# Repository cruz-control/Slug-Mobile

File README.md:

# Slug-Mobile

Slug Mobile: One Tenth Scale Autonomous Vehicle

CARLA gym environment: <https://github.com/cruz-control/carla-gym-env.git>

## Get Stated

Run the following command to install all the dependencies

```bash
pip3 install -r requirements.txt
```

Next you can run `main.py` to start the code.

## Setup Car

### Sensor Mount

Here's a link to the CAD for the sensor mount: [OnShape Link](https://cad.onshape.com/documents/b2439afa538affcdb2ce625c/w/6e13cd6ddc2a3739fa3b2738/e/3fdea52f99cf651c55640d90?renderMode=0&uiState=669d97643e0ca32c1d4d6b9b)

### Electrical System

We have included the custom power distribution board we created to the `power_dist_board` folder, the schematics show how to connect the different components.

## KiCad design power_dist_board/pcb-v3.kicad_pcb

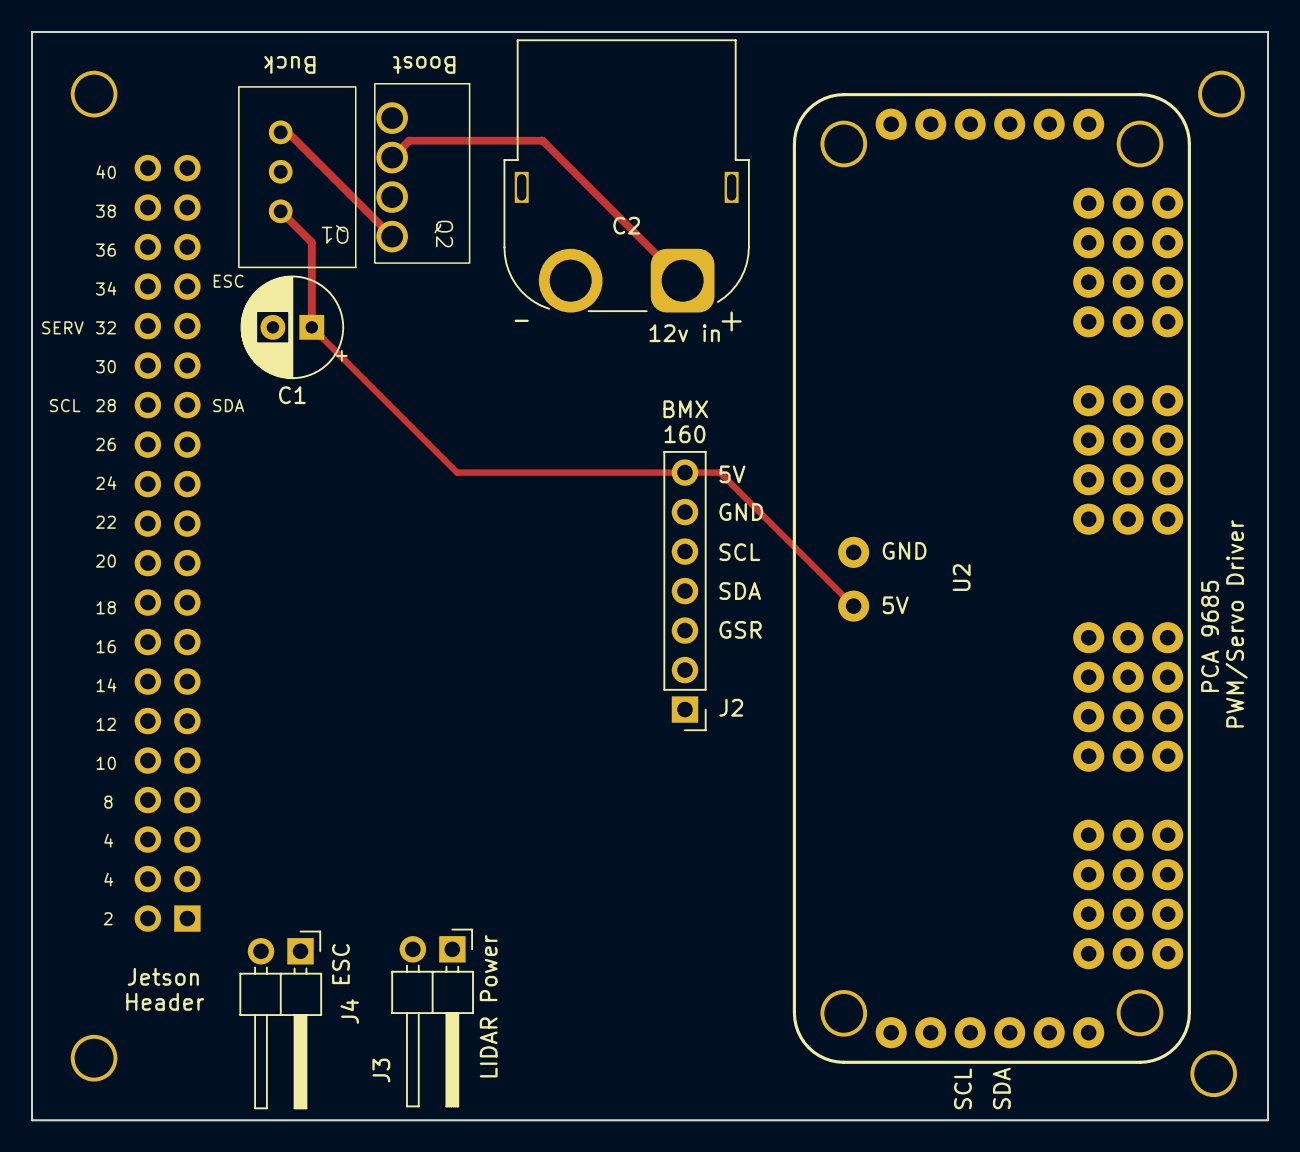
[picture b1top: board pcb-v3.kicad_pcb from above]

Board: 4 copper layers, 79.5 x 70.0 mm, 9 parts (1 on the bottom side), 8 nets.

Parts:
C1: CP_Radial_D6.3mm_P2.50mm
C2: AMASS_XT60PW-F_1x02_P7.20mm_Horizontal
J2: Conn_01x07_Socket; PinHeader_1x07_P2.54mm_Vertical
J3, J4: Screw_Terminal_01x02; PinHeader_1x02_P2.54mm_Horizontal
J5: Conn_02x20_Odd_Even; PinSocket_2x20_P2.54mm_Vertical
Q1: LC78_05-3.0
Q2: CRE1S Boost Converter
U2: Adafruit PCA9685 rev C (1)

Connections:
+3.3V: J5.1, J5.17
+5V: C1.1, J2.7, Q1.3 (Vout), U2.24 (A5)
+12V: C2.1 (Vin), Q2.2 (+Vin)
ESC: J4.1, J5.33
GND: C1.2, C2.2 (Vout), J2.3, J2.6, J3.2, J4.2, J5.6, J5.9, J5.14, J5.20, J5.25, J5.30, J5.34, J5.39, Q1.2 (GND), Q2.1 (-Vin), Q2.3 (-Vout), U2.14 (GND), U2.25 (EXTCLK)
SCL: J2.5, J5.28, U2.4 (A3)
SDA: J2.4, J5.27, U2.3 (A2)
STABLE_12V: J3.1, Q1.1 (Vin), Q2.4 (+Vout)

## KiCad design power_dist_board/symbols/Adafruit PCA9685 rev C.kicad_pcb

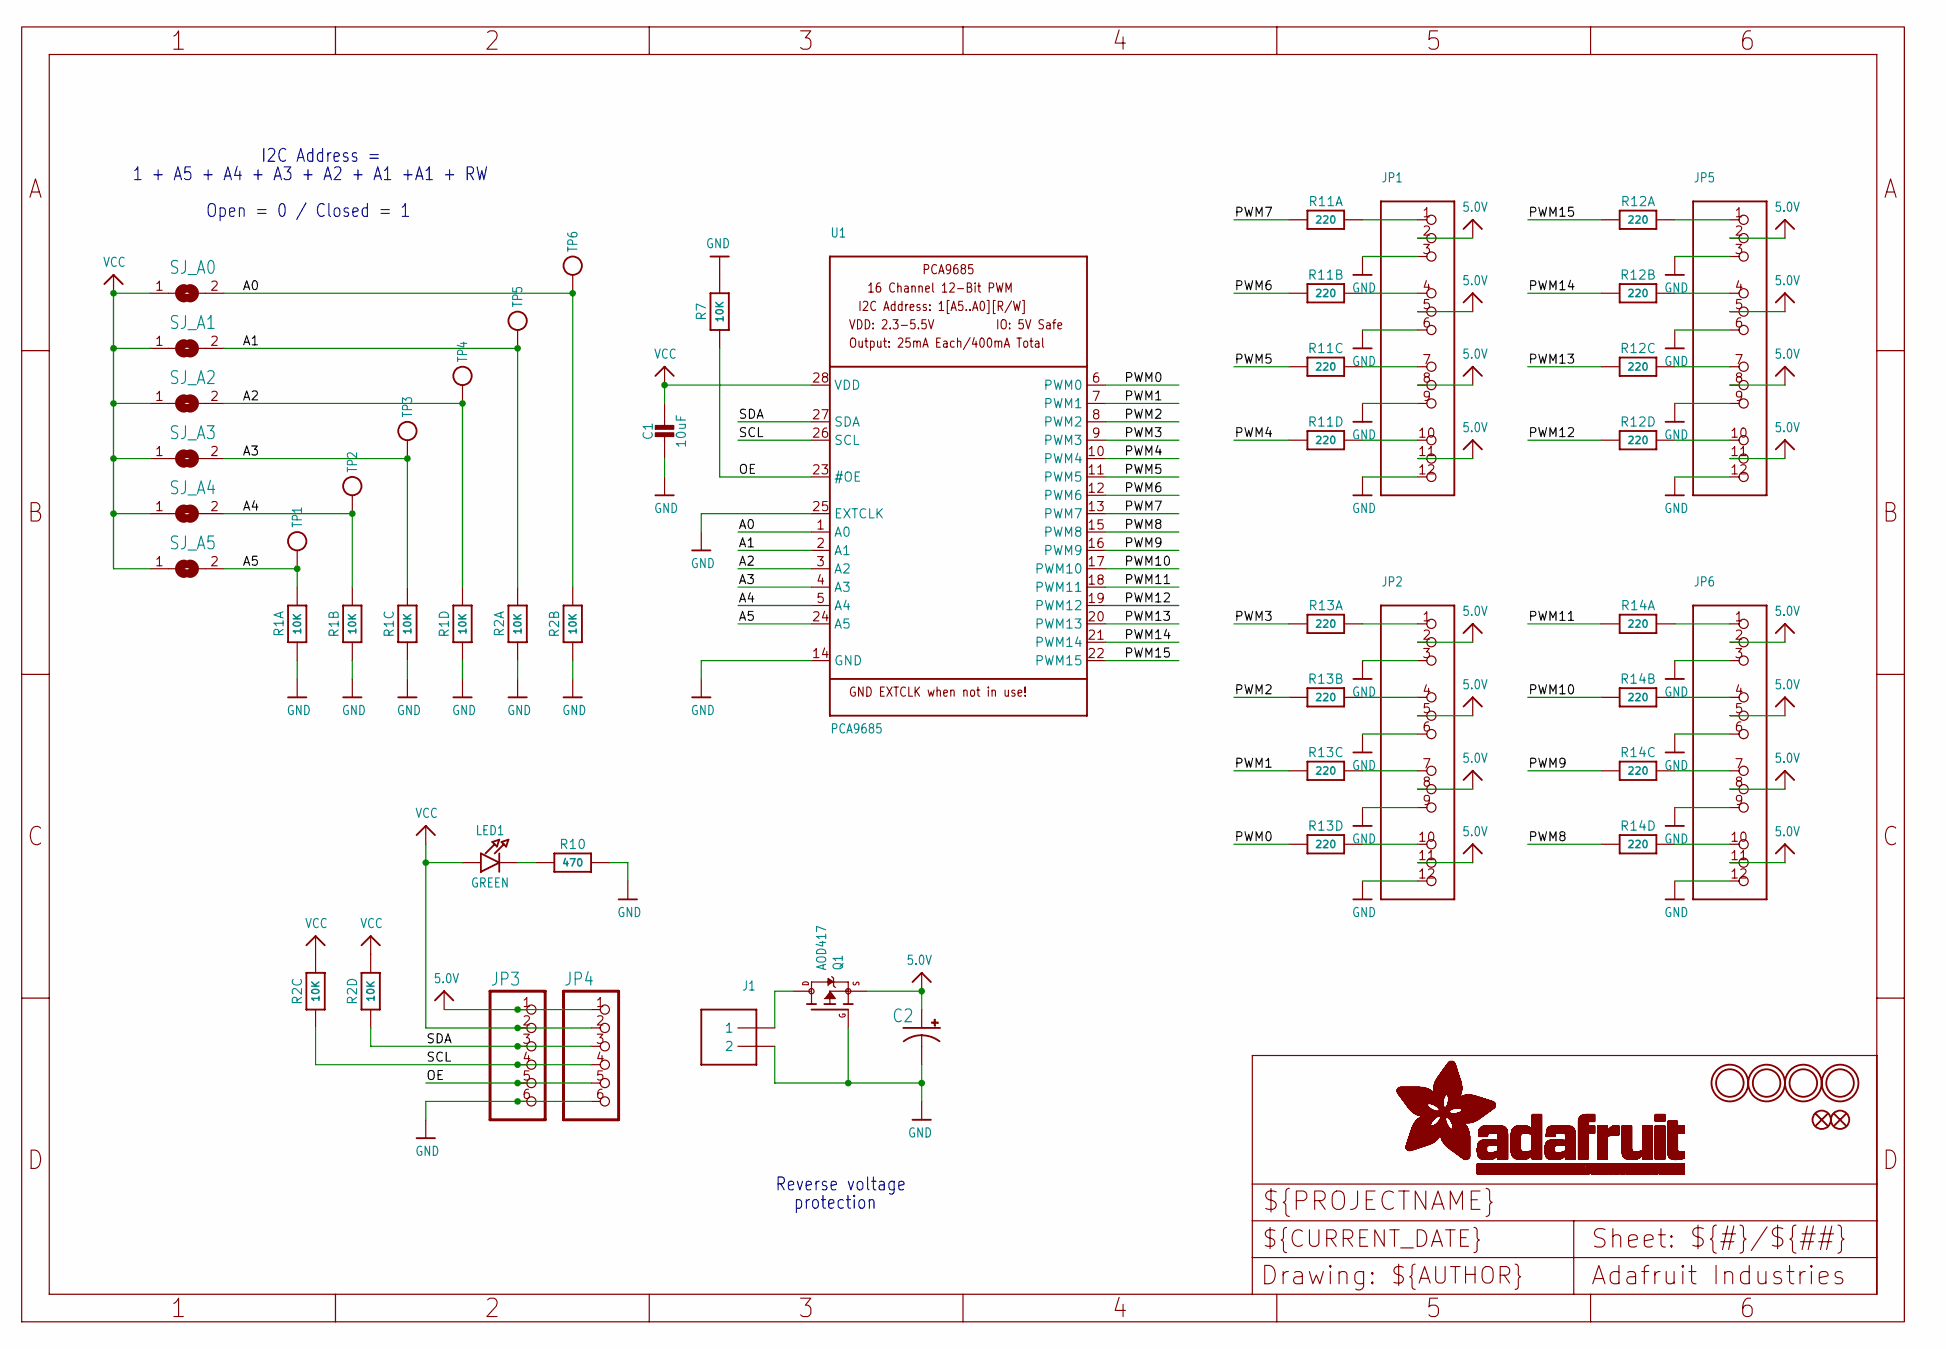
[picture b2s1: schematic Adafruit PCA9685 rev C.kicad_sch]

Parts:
C1: 10uF; 0805-NO
C2: CPOL-USE3.5-8; E3,5-8
FID1, FID2: FIDUCIAL""; FIDUCIAL_1MM
J1: TERMBLOCK_1X2; TERMBLOCK_1X2-3.5MM
JP1, JP2, JP5, JP6: HEADER-3X04; 3X04
JP3, JP4: PINHD-1X6CB; 1X06-CLEANBIG
LED1: GREEN; CHIPLED_0805_NOOUTLINE
Q1: AOD417; TO252
R1, R2: 10K; RESPACK_4X0603
R7: 10K; 0805-NO
R10: 470; _0805MP
R11, R12, R13, R14: 220; RESPACK_4X0603
SJ_A0, SJ_A1, SJ_A2, SJ_A3, SJ_A4, SJ_A5: SOLDERJUMPERREFLOW_NOPASTE; SOLDERJUMPER_REFLOW_NOPASTE
TP1, TP2, TP3, TP4, TP5, TP6: TESTPOINTROUND1MM; TESTPOINT_ROUND_1MM
U1: PCA9685; TSSOP28
U$47, U$48, U$49, U$50: MOUNTINGHOLE2.5; MOUNTINGHOLE_2.5_PLATED

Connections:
5.0V: C2.+, JP1.2, JP1.5, JP1.8, JP1.11, JP2.2, JP2.5, JP2.8, JP2.11, JP3.1, JP4.1, JP5.2, JP5.5, JP5.8, JP5.11, JP6.2, JP6.5, JP6.8, JP6.11, Q1.2 (S)
/A0: R2.7 (2), SJ_A0.2, TP6.P$1, U1.1 (A0)
/A1: R2.8 (2), SJ_A1.2, TP5.P$1, U1.2 (A1)
/A2: R1.5 (2), SJ_A2.2, TP4.P$1, U1.3 (A2)
/A3: R1.6 (2), SJ_A3.2, TP3.P$1, U1.4 (A3)
/A4: R1.7 (2), SJ_A4.2, TP2.P$1, U1.5 (A4)
/A5: R1.8 (2), SJ_A5.2, TP1.P$1, U1.24 (A5)
/OE: JP3.5, JP4.5, R7.1, U1.23 (#OE)
/PWM0: R13.4 (1), U1.6 (PWM0)
/PWM1: R13.3 (1), U1.7 (PWM1)
/PWM2: R13.2 (1), U1.8 (PWM2)
/PWM3: R13.1, U1.9 (PWM3)
/PWM4: R11.4 (1), U1.10 (PWM4)
/PWM5: R11.3 (1), U1.11 (PWM5)
/PWM6: R11.2 (1), U1.12 (PWM6)
/PWM7: R11.1, U1.13 (PWM7)
/PWM8: R14.4 (1), U1.15 (PWM8)
/PWM9: R14.3 (1), U1.16 (PWM9)
/PWM10: R14.2 (1), U1.17 (PWM10)
/PWM11: R14.1, U1.18 (PWM11)
/PWM12: R12.4 (1), U1.19 (PWM12)
/PWM13: R12.3 (1), U1.20 (PWM13)
/PWM14: R12.2 (1), U1.21 (PWM14)
/PWM15: R12.1, U1.22 (PWM15)
/SCL: JP3.4, JP4.4, R2.3 (1), U1.26 (SCL)
/SDA: JP3.3, JP4.3, R2.4 (1), U1.27 (SDA)
GND: C1.2, C2.-, J1.2, JP1.3, JP1.6, JP1.9, JP1.12, JP2.3, JP2.6, JP2.9, JP2.12, JP3.6, JP4.6, JP5.3, JP5.6, JP5.9, JP5.12, JP6.3, JP6.6, JP6.9, JP6.12, Q1.1 (G), R1.1, R1.2 (1), R1.3 (1), R1.4 (1), R2.1, R2.2 (1), R7.2, R10.2, U1.14 (GND), U1.25 (EXTCLK)
unnamed: LED1.C, R10.1
unnamed: J1.1, Q1.3 (D)
unnamed: JP1.1, R11.8 (2)
unnamed: JP1.4, R11.7 (2)
unnamed: JP1.7, R11.6 (2)
unnamed: JP1.10, R11.5 (2)
unnamed: JP5.1, R12.8 (2)
unnamed: JP5.4, R12.7 (2)
unnamed: JP5.7, R12.6 (2)
unnamed: JP5.10, R12.5 (2)
unnamed: JP2.1, R13.8 (2)
unnamed: JP2.4, R13.7 (2)
unnamed: JP2.7, R13.6 (2)
unnamed: JP2.10, R13.5 (2)
unnamed: JP6.1, R14.8 (2)
unnamed: JP6.4, R14.7 (2)
unnamed: JP6.7, R14.6 (2)
unnamed: JP6.10, R14.5 (2)
VCC: C1.1, JP3.2, JP4.2, LED1.A, R2.5 (2), R2.6 (2), SJ_A0.1, SJ_A1.1, SJ_A2.1, SJ_A3.1, SJ_A4.1, SJ_A5.1, U1.28 (VDD)

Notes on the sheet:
protection
Reverse voltage
I2C Address =
Open = 0 / Closed = 1
1 + A5 + A4 + A3 + A2 + A1 +A1 + RW

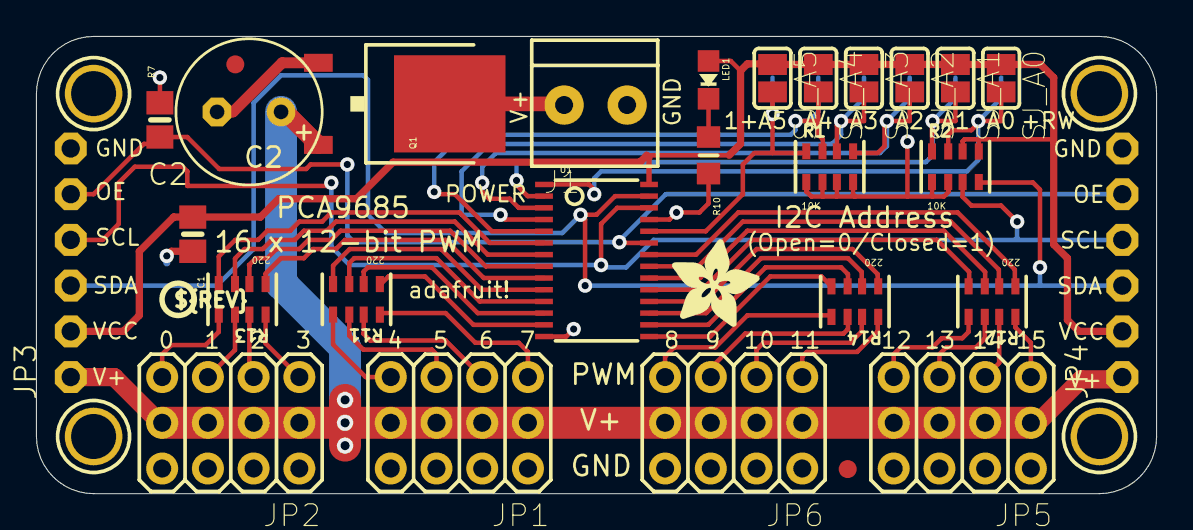
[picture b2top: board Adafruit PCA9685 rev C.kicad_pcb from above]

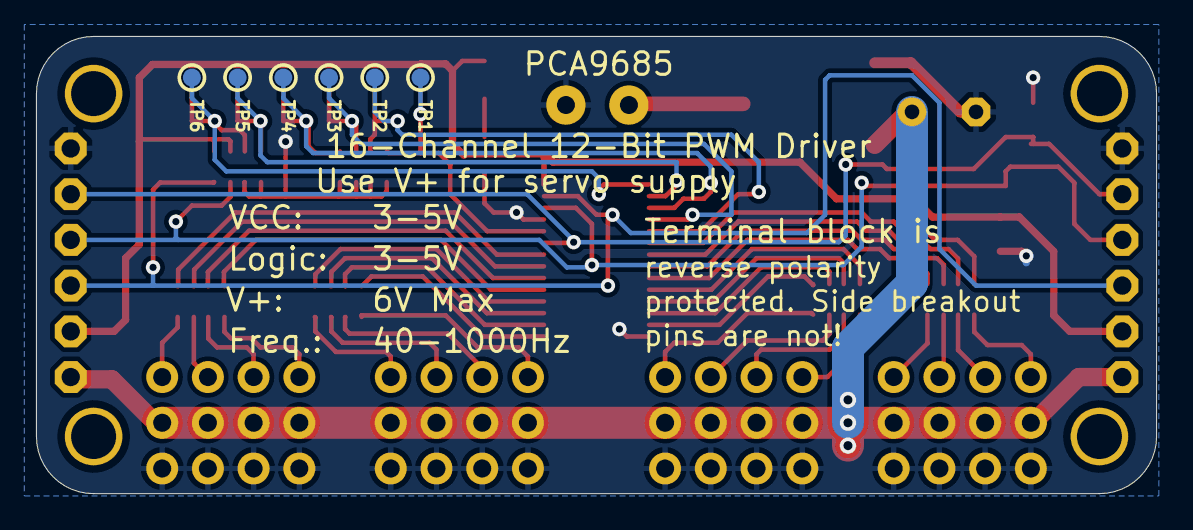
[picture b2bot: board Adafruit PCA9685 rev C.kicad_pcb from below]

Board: 2 copper layers, 62.2 x 25.4 mm, 40 parts (6 on the bottom side), 46 nets.

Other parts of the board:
U$51: ADAFRUIT_5MM
U$54: PCBFEAT-REV-040

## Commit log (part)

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2024-07-19 coked
2024-07-20 Added movement Cod3e
2024-07-21 Added get_rgb
2024-07-21 added power dist board
2024-07-21 added power dist board png
2024-07-21 Mount
2024-11-09 ServoKit package name changed
2024-11-15 Create all_sensors_main,py
    Runs LIDAR, RGB Camera, Event Camera, IMU, and Controller simultaneously
2024-11-15 Stores IMU data in a .csv
2024-11-15 IMU initializing and reading data
2024-11-15 camera 2 jpeg
2024-11-15 lidar reading and storing to .dat
2024-11-15 controlller 2 csv
2024-11-15 events 2 .dat
2024-11-15 imu 2 csv
2024-11-15 main
    Simultaneous lidar, imu, camera, event camera, and controller data collection and storage
2024-11-16 Add get event
2024-11-16 Add getting distance from LIDAR
2024-11-16 Get IMU data
2024-11-16 We need the IMU class in root too
2025-03-01 Remap Jetson pins and update labels
2025-04-24 Current code
2025-04-24 Update controller during loop
2025-04-24 Add PWM range to 1000-2000 us
2025-11-15 2025
2025-11-15 Update to kicad 9
2026-04-07 Sensor base class
2026-04-07 Complete move of old code
2026-04-07 Complete mv of old code
2026-04-07 lidar code
2026-04-07 Controller get_frames/update
2026-04-07 controler.py new with get_frames/update
2026-04-14 Updated lidar.py
2026-04-14 added code for IMU
2026-04-14 pubsub
2026-04-14 self, not slef
2026-04-14 Add main.py
2026-04-14 updated imu.py
2026-04-14 update sensor to node
2026-04-14 .gitignore
2026-04-14 start/stop
2026-04-26 Initialize motors.py
    Still waiting for controllers.py to be implemented. Until then, translated code from steer_drive.
2026-04-28 Fix controller and motor
2026-04-28 rgb.py up to pubsub system
    Needs review on the types of images taken. Sometimes you need grayscale, color, HSV format, etc. It may be worth commenting out the types of images we don't need to save on processing.
2026-05-05 Fix self bugs
2026-05-05 Add everything to main
2026-05-05 Fix typo
2026-05-05 Keep running on error
2026-05-05 Construct nodes in thread
2026-05-05 Less verbose errors
2026-05-05 no printf
2026-05-12 Typo fix
2026-05-12 added data logging
2026-05-12 now added data logging
2026-05-12 small fix
2026-05-12 Add loggers to main
2026-05-12 Fix bug
2026-05-12 Log lidar
2026-05-12 Log everything
2026-06-02 Fixes from pi
